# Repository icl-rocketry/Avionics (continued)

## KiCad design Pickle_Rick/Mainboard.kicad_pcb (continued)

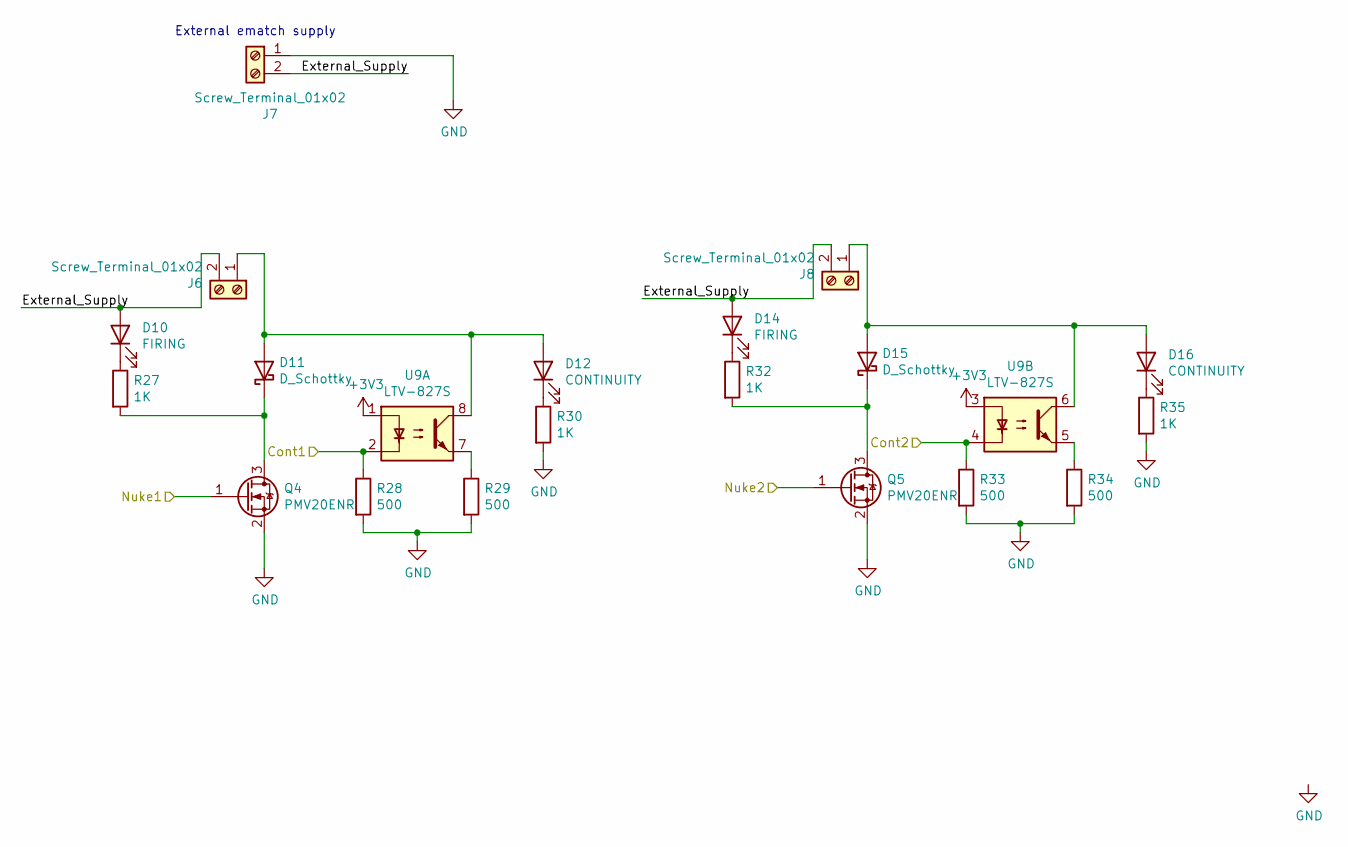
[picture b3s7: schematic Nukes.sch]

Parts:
D10, D14: FIRING; LED_0603_1608Metric_Castellated
D11, D15: D_Schottky; D_SOD-123F
D12, D16: CONTINUITY; LED_0603_1608Metric_Castellated
J6, J7, J8: Screw_Terminal_01x02; PHOENIX_1757242
Q4, Q5: PMV20ENR; SOT-23
R27, R30, R32, R35: 1K; R_0603_1608Metric
R28, R29, R33, R34: 500; R_0603_1608Metric
U9: LTV-827S; SMDIP-8_W9.53mm

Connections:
/Cont1: R28.1, U9.2; also elsewhere on the board
/Cont2: R33.1, U9.4; also elsewhere on the board
/Nuke1: Q4.1 (G); also elsewhere on the board
/Nuke2: Q5.1 (G); also elsewhere on the board
/nukes/External_Supply: D10.2 (A), D14.2 (A), J6.2, J7.2, J8.2
GND: J7.1, Q4.2 (S), Q5.2 (S), R28.2, R29.2, R30.2, R33.2, R34.2, R35.2; also elsewhere on the board
unnamed: D10.1 (K), R27.1
unnamed: D11.1 (K), Q4.3 (D), R27.2
unnamed: D11.2 (A), D12.2 (A), J6.1, U9.8
unnamed: D12.1 (K), R30.1
unnamed: D14.1 (K), R32.1
unnamed: D15.1 (K), Q5.3 (D), R32.2
unnamed: D15.2 (A), D16.2 (A), J8.1, U9.6
unnamed: D16.1 (K), R35.1
unnamed: R29.1, U9.7
unnamed: R34.1, U9.5

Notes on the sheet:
External ematch supply

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
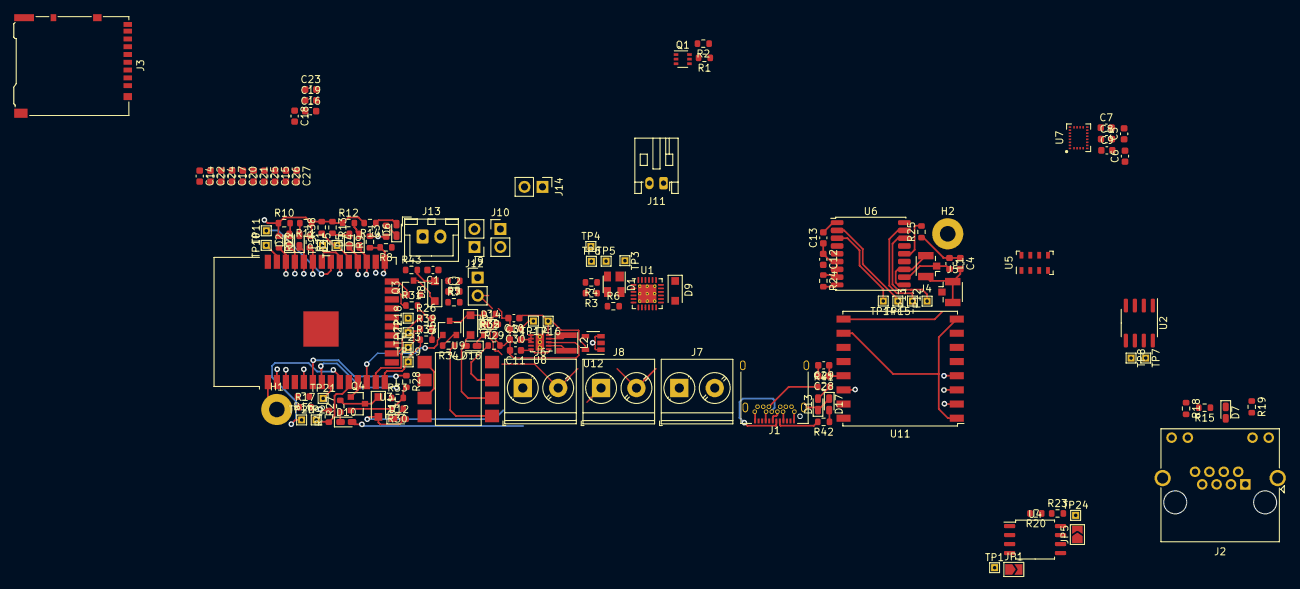
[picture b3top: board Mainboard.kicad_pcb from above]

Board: 4 copper layers, 150 parts (0 on the bottom side), 86 nets.

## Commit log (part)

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2020-12-03 imu tested and working
2020-12-03 updated python tools, fixed error in usb class
2020-12-03 updated detailed all
2020-12-03 fixed bugs
2020-12-03 Change serialization to little endian
2020-12-04 changed sensor classes to write directly to raw measurements structs
2020-12-05 Added basic plotter code
2020-12-05 modifiged gps to work
2020-12-06 Further plotter fixes
2020-12-07 fixed plotter.py
2020-12-12 Code stubs for logging
2020-12-15 removed unused libraries
2021-01-27 added callibration memebr function inside Sensors class to call individual snesor callibration routines
2021-01-31 Baro stuff
2021-01-31 added example code directory
2021-02-02 added sdfat library
2021-02-02 renamed sdfat library to sdfat-adafruit_fork
2021-02-09 added dimentiosn to ric pcb
2021-02-16 did a thing
2021-02-17 added pyro handler and seperated pyro types into different classes. Added more to storage controller and logging controller'
2021-02-18 updated systemstatus class to log raised flags. Added logging for all state transitions
2021-02-19 added pretty printing for routingtable
2021-02-19 added directory for python backend
2021-02-19 added comment to preallocation of routing table
2021-02-20 added circular buffer
2021-02-20 bugfix
2021-02-23 updated venv contents and created api_interface.py;
2021-02-23 Added comments
2021-02-23 added itervar class
2021-02-23 it works.. maybe i should delete this code forever
2021-02-24 uncommented stuff
2021-02-27 added placeholder for engine
2021-02-28 updated all packets to use new framework
2021-03-02 Started populating telemetry_logframe class
2021-03-02 Log frame should now serialise
2021-03-03 added code for microsd writing
2021-03-03 changed all log buffers back to vectors - system log is functional
2021-03-06 fixed led circuit/made sure cc pins are independent
2021-03-06 added ls functionality to storage controller
2021-03-06 Added sd card and more changes
2021-03-09 something idk maybe justa white sapce\
2021-03-09 Added USB
2021-03-09 Added mit logo to ricardo board. added wipe functionality to storage controller
2021-03-11 added doxygen for documentation
2021-03-12 added sparkfun ublox library
2021-03-16 Finished schematic; starting pcb design
2021-03-16 did some pcb thing
2021-03-16 Fixed alot of bugs
2021-03-18 added telemetry log rate function and rearranged objects in statemachine so they dont pass in the statemachine pointer
2021-03-19 updated storage controller write function to return a File
2021-03-20 added critical silkscreen + circuitry around esp mostly done
2021-03-21 completed melodyClass
2021-03-22 pchanged melody_t to perform implict cast to melody_base_t
2021-03-22 updated melody library
2021-03-22 Small change
2021-03-24 gcs_testing
2021-03-27 not getting farther...
    need to double check the buzzer, DS suggests 2 resistors
2021-03-27 updated platformio.ini to exclude Events_debian
2021-03-29 trying to fix memory leaks
2021-03-30 made something working
2021-03-30 more updates
2021-03-30 chagned lora receive
2021-03-31 updated python
2021-04-01 oh well it doesnt work agian
2021-04-01 enabled crc
2021-04-02 enabled telemtry logging to see affect on response
2021-04-08 added socketio
2021-05-06 moved to espidf with arduino as component
2021-05-06 added fireflies melody
2021-05-07 broken logging into more logical objects
2021-05-07 fmade sure log controller will generatea a unique directory even if the storage devices get wiped
2021-05-08 improving latency
2021-05-09 reconfiguring for remote gbd host
2021-05-10 merge
2021-05-11 Madgwick Implemented needs tuning
2021-05-11 it almost fits (☉_☉) ...
2021-05-14 fixed eigen library to work with arduino framework
2021-05-15 added linear acceleration calculation in state
2021-05-17 Separate voltage supply for ESP32 and pyros
2021-05-18 fixed rbg port
2021-05-22 madgwick udpate
2021-05-27 removed doc from gitignore
2021-05-27 udpate
2021-05-29 updated .gitignore
2021-05-29 pcb routing
2021-06-02 tested sockio in threads and in processes/
2021-06-02 finished flaskinterface except for redis intergration. written majority of packethandler but also needs redis integration.
2021-06-03 finished cleanup methods for packet record
2021-06-03 resized pcb
2021-06-07 testing the backend
2021-06-08 added command and packet post requests as well as getting the response from the flask interface. Started the Curses TUI
2021-06-13 progress on tui
2021-06-14 ui with error logging and error display working
2021-06-19 redefined telemetry packet in full. Redefined telemetry log frame fully. Tested telemetry displayed over text ui
2021-06-19 testing gcs
2021-06-22 updated gcs for pi operation
2021-06-26 updated tunez handler with pause and skip functionality
2021-06-27 refactoring networkmanager
2021-06-29 lora rewrite to support async trasnmission
2021-07-02 refactored command handler
2021-07-04 updarte
2021-07-07 added confirm tone when storage erase is complete as this operation can take a long time
2021-07-09 added python graphing and example js socketio client on backend. starting trying to tune madgwick
2021-07-15 writen methods for localization kf
2021-07-16 Made a few adjustments
2021-07-16 added altitude measurement
2021-07-17 updated baro sensor so conversion is non blocking with oversampling
2021-09-01 removed boost
2021-09-10 rewritten serial interface using cobs encoding to prevent framing errors and converted usb interface to new networking framework
2021-09-13 fixed madgwick issues needs a little tuning still. added a socketio to redis adapter so the helper apps can be run on remote clients
2021-09-14 added map view to flask interface
2021-09-22 added full mag callibration routine using a best fit ellipsoid. Note the callibration is currently a blocking routing and ideally the 10 second data collection done before can be done asynchronously
2021-09-27 added new command packet type (mag cal packet type). Added saving of full mag cal coefficents
2021-09-29 updated .gitignore and requirements.txt
2021-09-30 venv cleanup
2021-09-30 removed bloat
2021-09-30 fixing venv being added to git
2021-09-30 fixed backend
2021-10-02 fixed socketio connection event to start broadcasting when connection to the telemetetry namepsace
2021-10-15 Forgot to connect a ground node on regulator. Fixed now
2021-11-13 Chore: Update .gitignore for VSCode
2021-11-16 stuff
2021-11-20 Chore: Ignore .vscode settings
2021-11-20 Refactor: Moved fronend directory location
2021-11-21 Feat: Add telemetry log csv parsing & emitting function
2021-11-28 Style: Add server module & app explainers
    (Code should work w/o this commit)
    * Re-organize packages to recommended sequence
    * Add comments to improve readability
2021-12-04 Chore: Add react-router-dom package for multipage app functionality
2021-12-07 update;
2021-12-09 added source_service to packet headers on both c++ and python ends. Need to rewrite python library properly. Pyro networking is mostly written now
2021-12-22 working on updating the idf framework used
2022-01-17 Bump numpy from 1.20.3 to 1.21.0 in /Ricardo_OS/Python_backend
    Bumps [numpy](https://github.com/numpy/numpy) from 1.20.3 to 1.21.0.
    - [Release notes](https://github.com/numpy/numpy/releases)
    - [Changelog](https://github.com/numpy/numpy/blob/main/doc/HOWTO_RELEASE.rst.txt)
    - [Commits](https://github.com/numpy/numpy/compare/v1.20.3...v1.21.0)
    ---
    updated-dependencies:
2022-01-17 readded librnp as submodule
2022-01-18 merged new_IDF branch
2022-01-18 readded librnp
2022-01-18 cleaned up flask interface and how background tasks are started. Created an emitter class so that the dummy signal task can be killed gracefully. Fixed emitter emiting telemetry packet as "package", 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
2022-01-18 added list running tasks on cmd interface
2022-01-21 added pylibrnp
2022-01-21 Bump tmpl from 1.0.4 to 1.0.5 in /Ricardo_OS/Python_backend/frontend
    Bumps [tmpl](https://github.com/daaku/nodejs-tmpl) from 1.0.4 to 1.0.5.
    - [Release notes](https://github.com/daaku/nodejs-tmpl/releases)
    - [Commits](https://github.com/daaku/nodejs-tmpl/commits/v1.0.5)
    ---
    updated-dependencies:
    - dependency-name: tmpl
2022-01-21 updated all python apps to use new pylibrnp library
2022-01-22 Bump nanoid from 3.1.20 to 3.2.0 in /Ricardo_OS/Python_backend/frontend
    Bumps [nanoid](https://github.com/ai/nanoid) from 3.1.20 to 3.2.0.
    - [Release notes](https://github.com/ai/nanoid/releases)
    - [Changelog](https://github.com/ai/nanoid/blob/main/CHANGELOG.md)
    - [Commits](https://github.com/ai/nanoid/compare/3.1.20...3.2.0)
    ---
    updated-dependencies:
2022-01-29 C-style casts bad
2022-02-14 added pickle rick
2022-02-15 Added LMR14050 buck converter to pickle rick
2022-02-28 Bump url-parse in /Ricardo_OS/Python_backend/frontend
    Bumps [url-parse](https://github.com/unshiftio/url-parse) from 1.5.1 to 1.5.10.
    - [Release notes](https://github.com/unshiftio/url-parse/releases)
    - [Commits](https://github.com/unshiftio/url-parse/compare/1.5.1...1.5.10)
    ---
    updated-dependencies:
    - dependency-name: url-parse
2022-03-10 fixed a bug in radio.h
2022-03-22 pickle layed out
2022-03-28 pickle ready for review
2022-03-28 pcikle
2022-04-01 final changes to pick rick
2022-04-04 started writing udpadapter for sim data input
2022-04-06 Bump nanoid from 3.1.20 to 3.3.2 in /Ricardo_OS/Python_backend/frontend
    Bumps [nanoid](https://github.com/ai/nanoid) from 3.1.20 to 3.3.2.
    - [Release notes](https://github.com/ai/nanoid/releases)
    - [Changelog](https://github.com/ai/nanoid/blob/main/CHANGELOG.md)
    - [Commits](https://github.com/ai/nanoid/compare/3.1.20...3.3.2)
    ---
    updated-dependencies:
2022-04-07 Rewrote new sensor libraries for pickle rick. Restructured sensors and estimator classes to allow for threadsafe extension in the future.
2022-04-07 switched vspi and hspi labels so they are consistent with documentation
2022-04-07 fixed issue with udpadapter printing cobs instead of decoded data
2022-04-08 added HITL service in sensor manage
2022-04-11 Integrated Events, deployment, engines and control systems onto ricardo OS. modified log controller to send human readable message packets to ground station when system log ging for debugging ease. M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
2022-05-15 updated localization kf to 9 state formulation with baro and high-g accel measurement updates also included
2022-05-24 pavol is dumb
2022-05-26 added i2c pyro config to deployment handler!
2022-06-05 wrote can bus interface. should work but needs testing
2022-06-22 Bump numpy from 1.21.0 to 1.22.0 in /Ricardo_OS/Python_backend
    Bumps [numpy](https://github.com/numpy/numpy) from 1.21.0 to 1.22.0.
    - [Release notes](https://github.com/numpy/numpy/releases)
    - [Changelog](https://github.com/numpy/numpy/blob/main/doc/HOWTO_RELEASE.rst)
    - [Commits](https://github.com/numpy/numpy/compare/v1.21.0...v1.22.0)
    ---
    updated-dependencies:
2022-06-27 added i2c comms to mag class as mag seems to not work over spi, currently debugging this.
2022-06-27 fixing large commit
